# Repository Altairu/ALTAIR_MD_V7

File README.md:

# [**AltairMD_V7**](https://github.com/Altairu/AltairMD_V7)

https://github.com/Altairu/AltairMD_V7
---
### **仕様**
* 30V~10V(フォトカプラを変更すると10V以下も可)
* 最大40A 

|SDs|Ps1|Ps2|出力|
|:----:|:----:|:----:|:----:|
|HIGH|LOW	|LOW	|停止|
|HIGH|LOW	|HIGH	|逆転|
|HIGH|HIGH	|LOW	|正転|
|HIGH|HIGH	|HIGH	|`ブレーキ`（非推奨）|
|LOW|X	|X	|0|
### **降圧**

### **三端子レギュレーター** 
### **[NJM7812SDL1]()**
* **12Vに降圧**
* **端子が3つ(入力・グラウンド・出力）**
* **三端子レギュレータは落とした分の電圧をすべて`熱`として消費**
* **ダイオード**
レギュレータに逆電流が流れるのを防止
* **コンデンサ**
コンデンサは入力側と出力側に0.1～10[uF]程度入れるのが一般的

---
## **フォトカプラ**

### [TLP152](https://akizukidenshi.com/catalog/g/g110824/)
* 取り付け様式:	SMD/SMT	
* パッケージ/ケース:SOIC-6
* 電源電圧min.：10V
* 電源電圧max.：30V
* 出力電流：2A
* 入力電流max.：20mA
* 上昇応答時間：95ns
* 下降応答時間：110ns

---
## **MOSFET**
[**RSJ400N10**](https://www.rohm.co.jp/products/mosfets/small-signal/single-nch/rsj400n10-product)
Nch 100V 40A Power MOSFET

* 4V駆動タイプ
* Nチャンネル　パワーMOSFET
* 高速スイッチング
* 駆動回路が簡単
* 並列使用が容易

ゲート抵抗は10[Ω]で設定している

---
### **ハーフブリッジゲートドライバ**
### [**IR2302STRPBF**](https://akizukidenshi.com/catalog/g/g115656/)

* IN端子
ハイサイドMOSFETをONにするか、ローサイドMOSFETをONにするかの切り替えを行う
Hが入力されるとハイサイド、Lが入力されるとローサイドがONとなる
**ハイサイドにNchMOSFETを使うためにブーストラップ回路を使用**
* ブートストラップコンデンサの容量は[10uF]
* ブートストラップダイオード
(ファストリカバリダイオード)
* `100％出力は不可`
ブートストラップ回路の制約で
コンデンサのチャージ時間が必要.

# Ｈブリッジ回路

---
<br>
<br>

| Ps1 | Ps2 | Q1  | Q2  | Q3  | Q4  | 1    | 2    | 
| :----: | :----: | :----: | :----: | :----: | :----: | :----: | :----: | 
| L   | L   | H   | L   | H   | L   | open | open | 
| L   | H   | H   | H   | L   | L   | L    | H    | 
| H   | L   | L   | L   | H   | H   | H    | L    | 
| H   | H   | H   | H   | H   | H   | L    | L    |

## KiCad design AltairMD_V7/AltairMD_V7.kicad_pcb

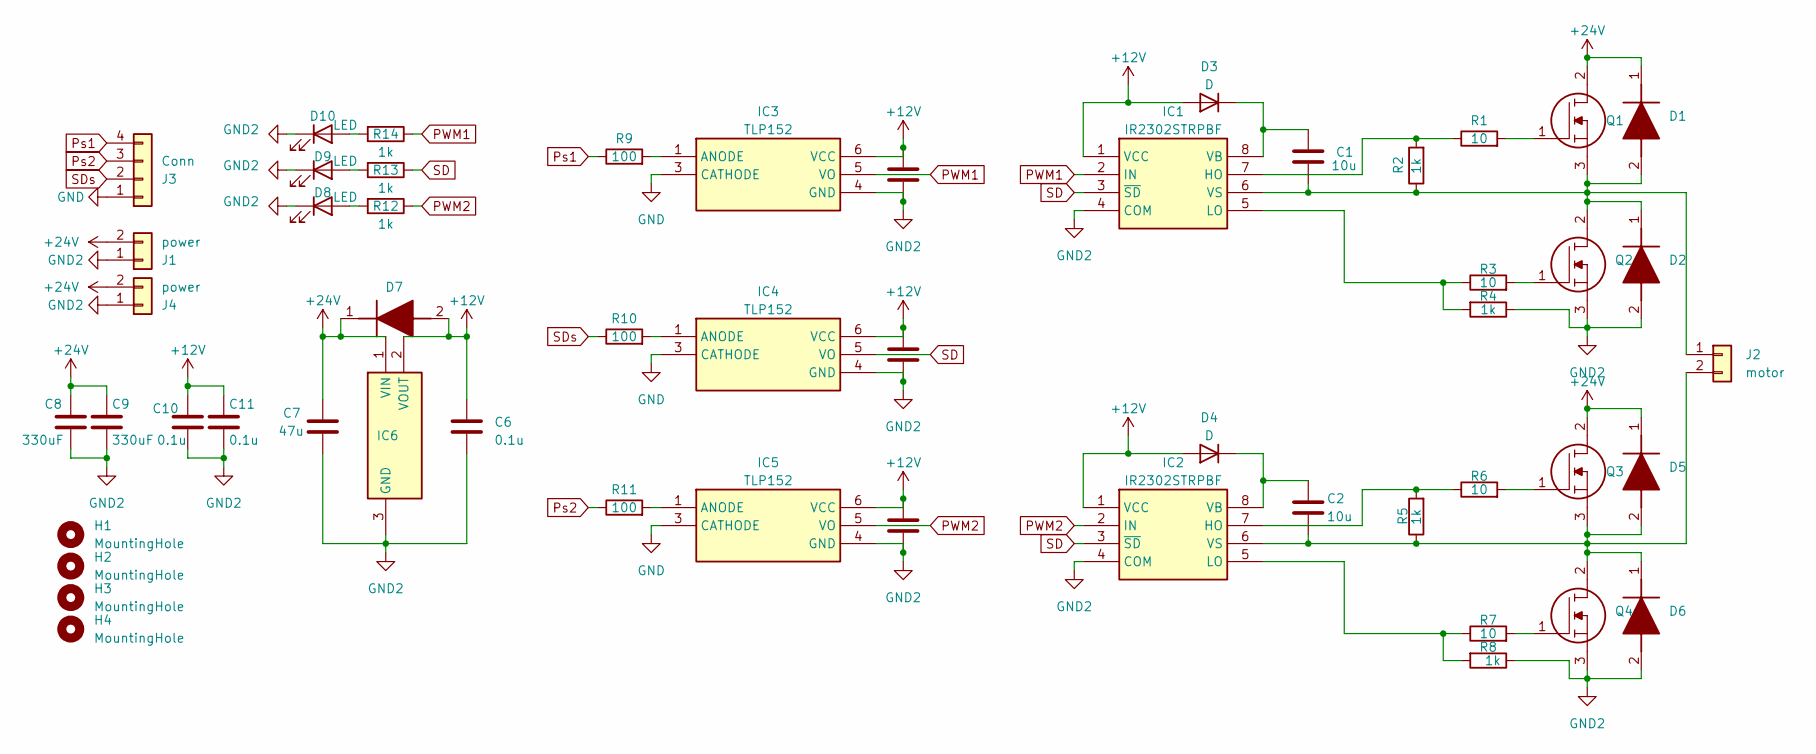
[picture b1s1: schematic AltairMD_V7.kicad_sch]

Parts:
C1, C2: 10u; C_0603_1608Metric
C3, C4, C5, C6, C10, C11: 0.1u; C_0603_1608Metric
C7: 47u; C_0603_1608Metric
C8, C9: 330uF; CP_Elec_10x10
D1, D2, D5, D6, D7: RF201LAM2STR; Manufacturer_Part_Number RF201LAM2STR
D3, D4: D; D_0603_1608Metric
D8, D9, D10: LED; LED_0603_1608Metric
H1, H2, H3, H4: MountingHole; MountingHole_3.2mm_M3
IC1, IC2: IR2302STRPBF; SOIC127P600X175-8N; Manufacturer_Part_Number IR2302STRPBF
IC3, IC4, IC5: TLP152; 11-4L1S_5-PIN-SOIC_; Manufacturer_Part_Number TLP152
IC6: NJM7800S-DL1; TO-252-3-L1; Manufacturer_Part_Number NJM7800S-DL1
J1, J4: power; AMASS_XT60PW-M_1x02_P7.20mm_Horizontal
J2: motor; AMASS_XT60PW-F_1x02_P7.20mm_Horizontal
J3: Conn; JST_XA_S04B-XASK-1_1x04_P2.50mm_Horizontal
Q1, Q2, Q3, Q4: RSJ400N06FRATL; R6024KNJTL; Manufacturer_Part_Number RSJ400N06FRATL
R1, R3, R6, R7: 10; R_0603_1608Metric
R2, R4, R5, R8, R12, R13, R14: 1k; R_0603_1608Metric
R9, R10, R11: 100; R_0603_1608Metric

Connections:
+12V: C3.1, C4.1, C5.1, C6.1, C10.1, C11.1, D3.2 (A), D4.2 (A), D7.2 (A), IC1.1 (VCC), IC2.1 (VCC), IC3.6 (VCC), IC4.6 (VCC), IC5.6 (VCC), IC6.2 (VOUT)
+24V: C7.1, C8.1, C9.1, D1.1 (K), D5.1 (K), D7.1 (K), IC6.1 (VIN), J1.2, J4.2, Q1.2, Q3.2
GND: IC3.3 (CATHODE), IC4.3 (CATHODE), IC5.3 (CATHODE), J3.1
GND2: C3.2, C4.2, C5.2, C6.2, C7.2, C8.2, C9.2, C10.2, C11.2, D2.2 (A), D6.2 (A), D8.1 (K), D9.1 (K), D10.1 (K), IC1.4 (COM), IC2.4 (COM), IC3.4 (GND), IC4.4 (GND), IC5.4 (GND), IC6.3 (GND), J1.1, J4.1, Q2.3, Q4.3, R4.1, R8.1
unnamed: C1.2, D1.2 (A), D2.1 (K), IC1.6 (VS), J2.1, Q1.3, Q2.2, R2.1
unnamed: C1.1, D3.1 (K), IC1.8 (VB)
unnamed: C2.1, D4.1 (K), IC2.8 (VB)
unnamed: C2.2, D5.2 (A), D6.1 (K), IC2.6 (VS), J2.2, Q3.3, Q4.2, R5.1
unnamed: D8.2 (A), R12.2
unnamed: D9.2 (A), R13.2
unnamed: D10.2 (A), R14.2
unnamed: IC1.7 (HO), R1.1, R2.2
unnamed: IC1.5 (LO), R3.1, R4.2
unnamed: IC2.7 (HO), R5.2, R6.1
unnamed: IC2.5 (LO), R7.1, R8.2
unnamed: IC3.1 (ANODE), R9.2
unnamed: IC4.1 (ANODE), R10.2
unnamed: IC5.1 (ANODE), R11.2
unnamed: Q1.1, R1.2
unnamed: Q2.1, R3.2
unnamed: Q3.1, R6.2
unnamed: Q4.1, R7.2
PWM1: IC1.2 (IN), IC3.5 (VO), R14.1
PWM2: IC2.2 (IN), IC5.5 (VO), R12.1
Ps1: J3.4, R9.1
Ps2: J3.3, R11.1
SD: IC1.3 (~SD), IC2.3 (~SD), IC4.5 (VO), R13.1
SDs: J3.2, R10.1

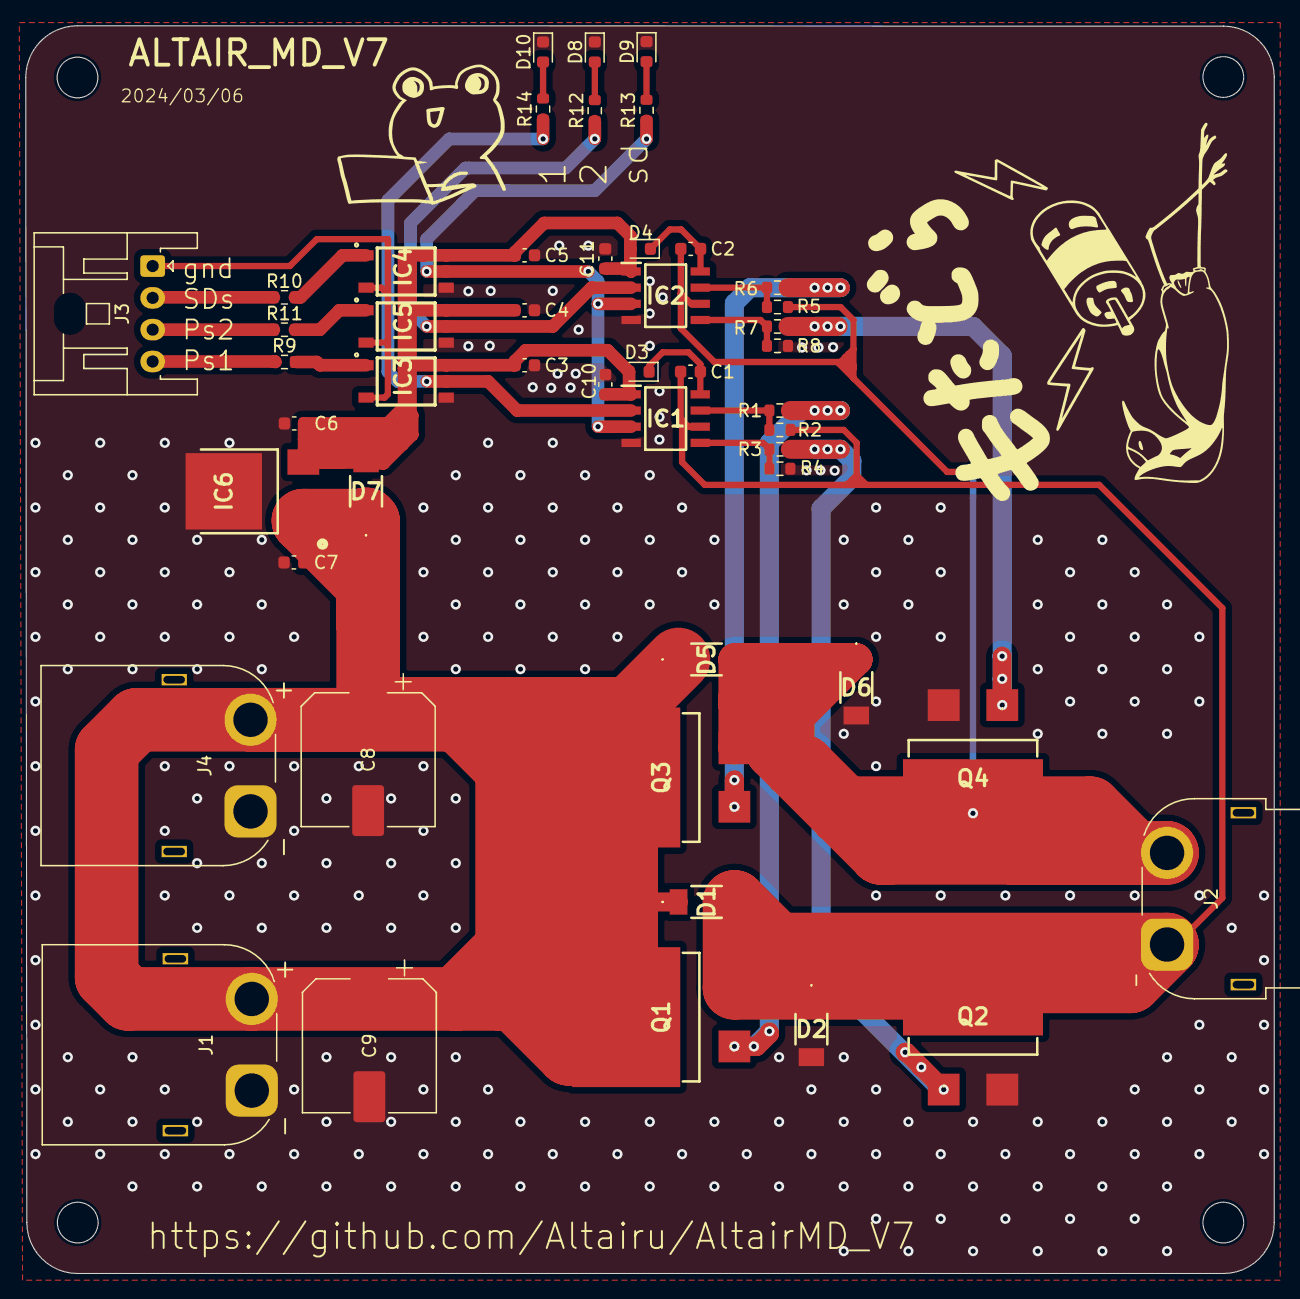
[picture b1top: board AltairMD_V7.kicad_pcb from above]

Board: 2 copper layers, 98.1 x 98.0 mm, 53 parts (0 on the bottom side), 28 nets.
